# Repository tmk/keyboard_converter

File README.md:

TMK Keyboard Converter PCB with Mini DIN connector
==================================================
This converts pre-modern keyboard protocols into modern USB using [TMK Keyboard Firmware Collection][tmk_keyboard].

[tmk_keyboard]: https://github.com/tmk/tmk_keyboard

You can buy assembled converter here. https://geekhack.org/index.php?topic=72052.0

Updates
-------
2016/07/03  Rev 2.4 Changed foot print of USB microB and Xtal
2015/09/29  Rev 2.2 Changed LED footprint

Supported Protocols
-------------------
See [this](https://github.com/tmk/tmk_keyboard#converter) for supported protocols.

### PS/2(ScanCode Set 2)
MiniDIN 6P

### Apple Desktop Bus
MiniDIN 4P

### Sharp X68000
MiniDIN 7P

### Sun Type3-5
MiniDIN 8P

### NEC PC98
MiniDIN 8P

### NeXT
MiniDIN 5P

Schematics
----------
[converter_schematic.pdf](converter_schematic.pdf)

PCB Revisions
-------------
### PCB rev1
[Rev1](Rev1.md) has lands for MiniDIN and IO pads for other interface than MiniDIN. With wire jumpers it can support many protocols.
It uses Atmel AVR ATmega32U4.

### PCB rev2
Rev2 is smaller and supports only protocols which uses MiniDIN connector and can be configured with solder jumpers on bottom of the board.
It uses Atmel AVR ATmega32U2.

### PCB rev2.1
Fixed misaligned pins of Mini DIN connector, clearance of solder mask and silk prints.

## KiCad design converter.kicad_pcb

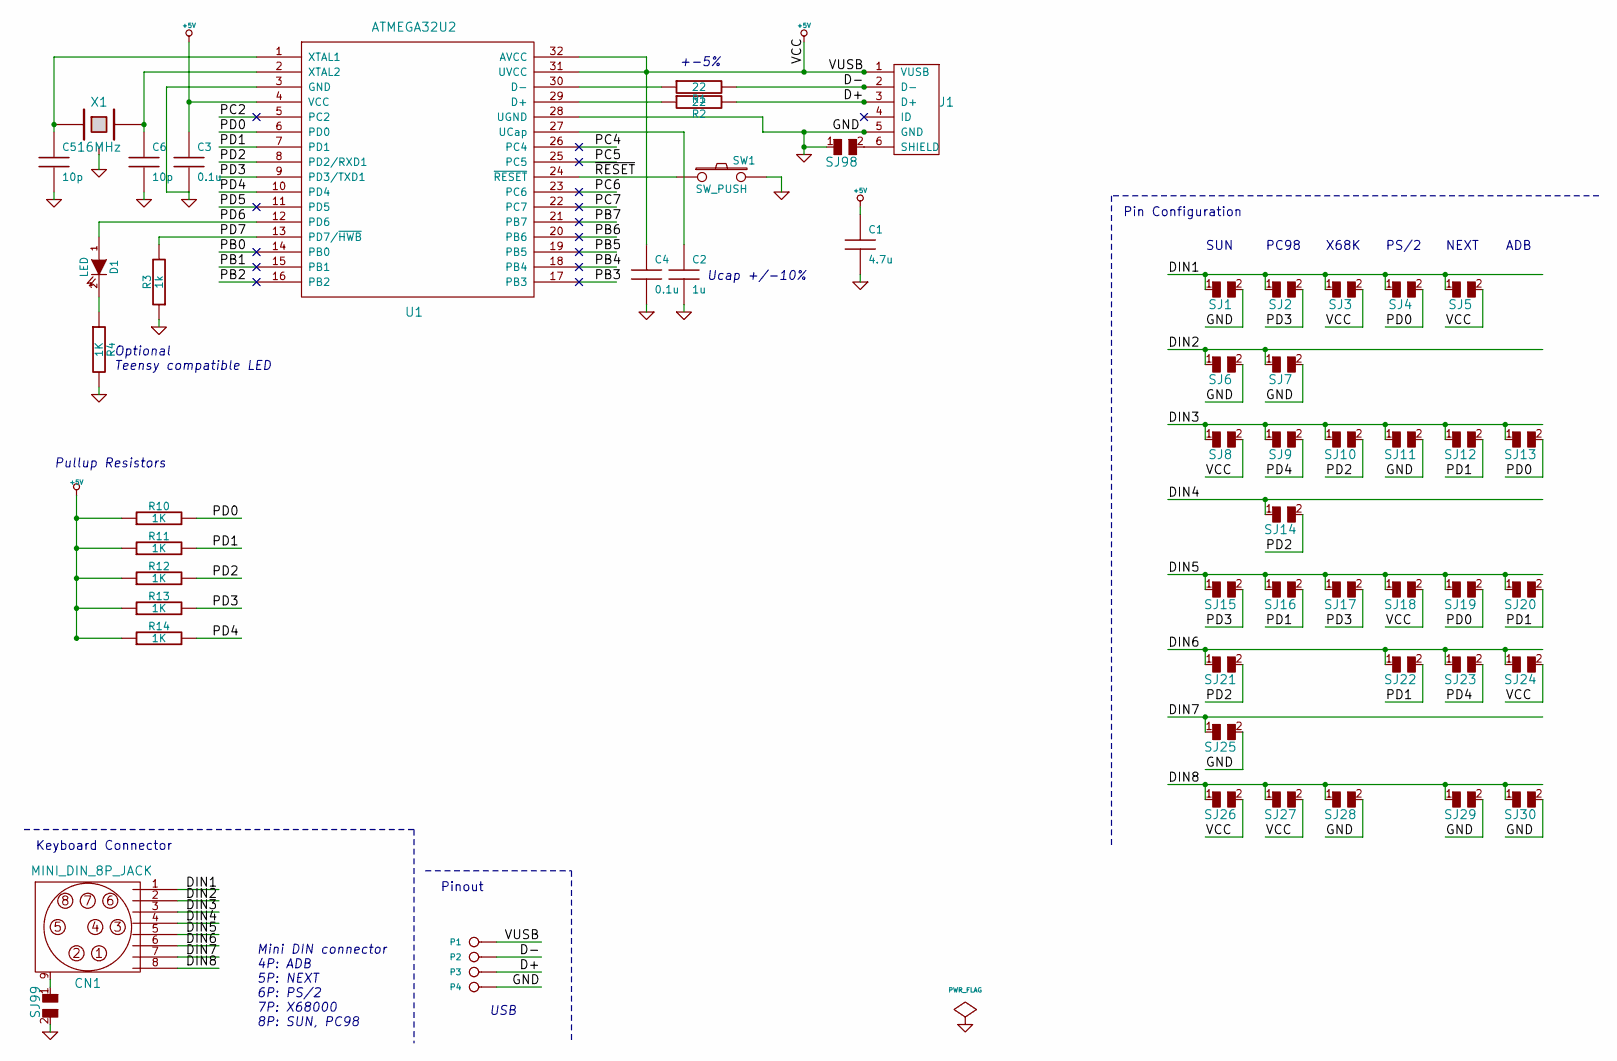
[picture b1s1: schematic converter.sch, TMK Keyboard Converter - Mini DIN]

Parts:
C1: 4.7u
C2: 1u
C3, C4: 0.1u
C5, C6: 10p
CN1: MINI_DIN_8P_JACK
D1: LED
J1: USB_mini_micro_B
P1, P2, P3, P4: CONN_1
R1, R2: 22
R3: 1k
R4, R10, R11, R12, R13, R14: 1K
SJ1, SJ2, SJ3, SJ4, SJ5, SJ6, SJ7, SJ8, SJ9, SJ10, SJ11, SJ12, SJ13, SJ14, SJ15, SJ16, SJ17, SJ18, SJ19, SJ20, SJ21, SJ22, SJ23, SJ24, SJ25, SJ26, SJ27, SJ28, SJ29, SJ30, SJ98, SJ99: SOLDER_JUMPER
SW1: SW_PUSH
U1: ATMEGA32U2
X1: 16MHz

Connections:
+5V: C1.1, C3.1, C4.1, J1.1 (VUSB), P1.1, R10.1, R11.1, R12.1, R13.1, R14.1, SJ3.2, SJ5.2, SJ8.2, SJ18.2, SJ24.2, SJ26.2, SJ27.2, U1.4 (VCC), U1.31 (UVCC), U1.32 (AVCC)
/D+: J1.3 (D+), P3.1, R2.2
/D-: J1.2 (D-), P2.1, R1.2
/DIN1: CN1.1, SJ1.1, SJ2.1, SJ3.1, SJ4.1, SJ5.1
/DIN2: CN1.2, SJ6.1, SJ7.1
/DIN3: CN1.3, SJ8.1, SJ9.1, SJ10.1, SJ11.1, SJ12.1, SJ13.1
/DIN4: CN1.4, SJ14.1
/DIN5: CN1.5, SJ15.1, SJ16.1, SJ17.1, SJ18.1, SJ19.1, SJ20.1
/DIN6: CN1.6, SJ21.1, SJ22.1, SJ23.1, SJ24.1
/DIN7: CN1.7, SJ25.1
/DIN8: CN1.8, SJ26.1, SJ27.1, SJ28.1, SJ29.1, SJ30.1
/PB0: U1.14 (PB0)
/PB1: U1.15 (PB1)
/PB2: U1.16 (PB2)
/PB3: U1.17 (PB3)
/PB4: U1.18 (PB4)
/PB5: U1.19 (PB5)
/PB6: U1.20 (PB6)
/PB7: U1.21 (PB7)
/PC2: U1.5 (PC2)
/PC4: U1.26 (PC4)
/PC5: U1.25 (PC5)
/PC6: U1.23 (PC6)
/PC7: U1.22 (PC7)
/PD0: R10.2, SJ4.2, SJ13.2, SJ19.2, U1.6 (PD0)
/PD1: R11.2, SJ12.2, SJ16.2, SJ20.2, SJ22.2, U1.7 (PD1)
/PD2: R12.2, SJ10.2, SJ14.2, SJ21.2, U1.8 (PD2/RXD1)
/PD3: R13.2, SJ2.2, SJ15.2, SJ17.2, U1.9 (PD3/TXD1)
/PD4: R14.2, SJ9.2, SJ23.2, U1.10 (PD4)
/PD5: U1.11 (PD5)
/PD6: D1.1 (A), U1.12 (PD6)
/PD7: R3.2, U1.13 (PD7/~HWB)
/~RESET: SW1.1, U1.24 (~RESET)
GND: C1.2, C2.2, C3.2, C4.2, C5.2, C6.2, J1.5 (GND), P4.1, R3.1, R4.2, SJ1.2, SJ6.2, SJ7.2, SJ11.2, SJ25.2, SJ28.2, SJ29.2, SJ30.2, SJ98.1, SJ99.2, SW1.2, U1.3 (GND), U1.28 (UGND), X1.3
unnamed: C2.1, U1.27 (UCap)
unnamed: C5.1, U1.1 (XTAL1), X1.1
unnamed: C6.1, U1.2 (XTAL2), X1.2
unnamed: CN1.9, SJ99.1
unnamed: D1.2 (K), R4.1
unnamed: J1.6 (SHIELD), SJ98.2
unnamed: R1.1, U1.30 (D-)
unnamed: R2.1, U1.29 (D+)

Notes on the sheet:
Pullup Resistors
Mini DIN connector 4P: ADB 5P: NEXT 6P: PS/2 7P: X68000 8P: SUN, PC98
USB
Ucap +/-10%
+-5%
Optional Teensy compatible LED
Keyboard Connector
PC98
X68K
PS/2
NEXT
ADB
SUN
Pin Configuration
Pinout

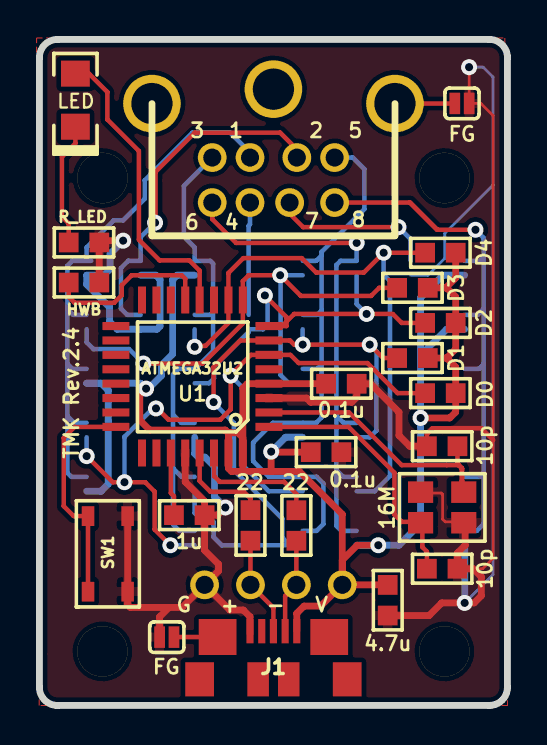
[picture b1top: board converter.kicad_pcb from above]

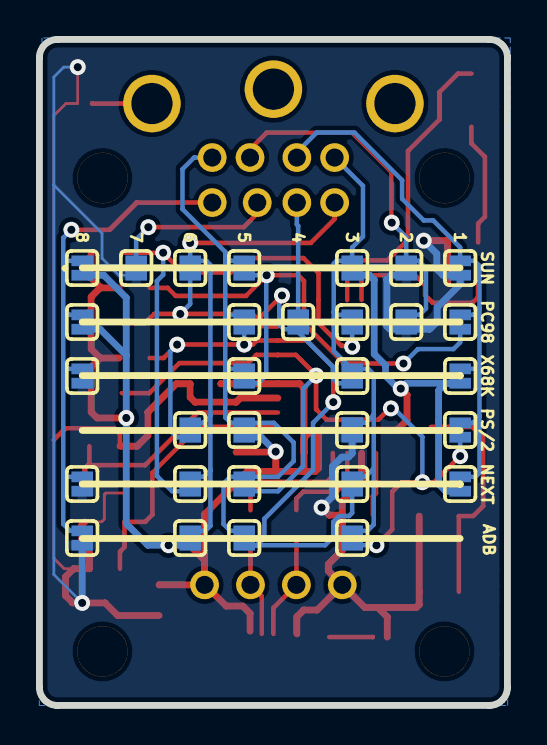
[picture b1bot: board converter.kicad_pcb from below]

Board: 2 copper layers, 26.0 x 37.0 mm, 61 parts (30 on the bottom side), 28 nets.

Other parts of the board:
HOLE_M2.6, HOLE_M2.6#2, HOLE_M2.6#3, HOLE_M2.6#4: VAL**; HOLE_M2.6

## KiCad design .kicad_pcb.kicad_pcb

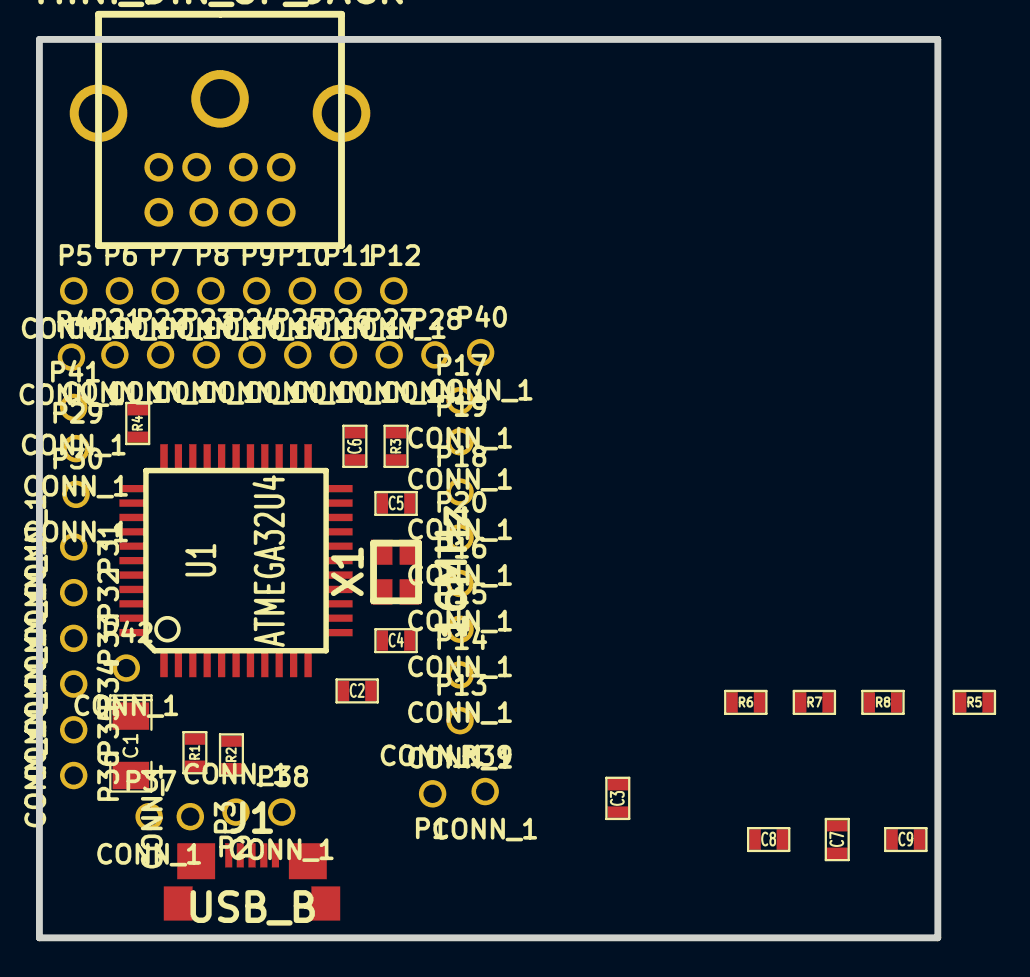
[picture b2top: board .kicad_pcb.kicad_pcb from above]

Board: 2 copper layers, 49.9 x 49.9 mm, 63 parts (0 on the bottom side), 45 nets, no tracks yet.

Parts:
C1: 10u; SM1206POL
C2: 1u; SM0603_Capa
C3, C6, C7, C8, C9: 0.1u; SM0603_Capa
C4, C5: 22p; SM0603_Capa
CN1: MINI_DIN_8P_JACK; MINI_DIN_8
J1: USB_B; USB_microB
P1, P2, P3, P4, P5, P6, P7, P8, P9, P10, P11, P12, P13, P14, P15, P16, P17, P18, P19, P20, P21, P22, P23, P24, P25, P26, P27, P28, P29, P30, P31, P32, P33, P34, P35, P36, P37, P38, P39, P40, P41, P42: CONN_1; PIN_1
R1, R2: 22; SM0603
R3: 10K; SM0603
R4: 1k; SM0603
R5, R6, R7, R8: 1K; SM0603
U1: ATMEGA32U4; TQFP44
X1: 16MHz; FA-238

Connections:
+5V: C1.1, C3.1, C7.1, C8.1, C9.1, J1.1, P4.1, P37.1, R3.1, R5.1, R6.1, R7.1, R8.1, U1.2, U1.7, U1.14, U1.24, U1.34, U1.44
/AREF: P42.1, U1.42
/D+: J1.3, P2.1, R2.2
/D-: J1.2, P3.1, R1.2
/DIN1: CN1.1, P5.1
/DIN2: CN1.2, P6.1
/DIN3: CN1.3, P7.1
/DIN4: CN1.4, P8.1
/DIN5: CN1.5, P9.1
/DIN6: CN1.6, P10.1
/DIN7: CN1.7, P11.1
/DIN8: CN1.8, P12.1
/PB0: P13.1, U1.8
/PB1: P14.1, U1.9
/PB2: P15.1, U1.10
/PB3: P16.1, U1.11
/PB4: P20.1, U1.28
/PB5: P18.1, U1.29
/PB6: P19.1, U1.30
/PB7: P17.1, U1.12
/PC6: P29.1, U1.31
/PC7: P30.1, U1.32
/PD0: P21.1, R5.2, U1.18
/PD1: P22.1, R6.2, U1.19
/PD2: P23.1, R7.2, U1.20
/PD3: P24.1, R8.2, U1.21
/PD4: P25.1, U1.25
/PD5: P26.1, U1.22
/PD6: P27.1, U1.26
/PD7: P28.1, U1.27
/PE6: P41.1, U1.1
/PF0: P36.1, U1.41
/PF1: P35.1, U1.40
/PF4: P34.1, U1.39
/PF5: P33.1, U1.38
/PF6: P32.1, U1.37
/PF7: P31.1, U1.36
/~RESET: C6.1, P39.1, R3.2, U1.13
GND: C1.2, C2.2, C3.2, C4.2, C5.2, C6.2, C7.2, C8.2, C9.2, J1.5, P1.1, P38.1, P40.1, R4.1, U1.5, U1.15, U1.23, U1.35, U1.43
unnamed: R2.1, U1.4
unnamed: R1.1, U1.3
unnamed: R4.2, U1.33
unnamed: C2.1, U1.6
unnamed: C5.1, U1.17, X1.2
unnamed: C4.1, U1.16, X1.1

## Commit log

2013-04-30 Add initial files.
2013-04-30 Add Mini DIN 8P component
2013-05-01 Add converter.mod
2013-05-01 Assign footprint
2013-05-05 Wire component
2013-05-10 Rev1 for fusion PCB
2013-05-22 Clean temp files
2013-05-22 Remove wrong 3D model from PIN_1 module
2013-05-30 Fix library preference
2013-07-11 Clean up gerber files
2013-07-11 Add keyboard_parts.[lib|mod]
2014-03-23 Initial commit of PCB rev.2
2014-03-23 Add rev.2 gerber files.
2014-03-23 Clean library.
2014-03-24 Update Mini DIN module and vix PCB.
    - Wrong pad alignment
2014-04-28 Fix documents
2014-06-22 rev2.1
2014-07-05 Add schematic
2015-09-29 Change LED footprint and add numbering silks
2015-12-22 Change values of capacitors and solder mask setting
2016-07-03 Add dimensions for pcb edge.cuts
2016-07-03 Change foot print of Xtal
2016-07-03 Change foot print of USB_microB adding bottom pads
